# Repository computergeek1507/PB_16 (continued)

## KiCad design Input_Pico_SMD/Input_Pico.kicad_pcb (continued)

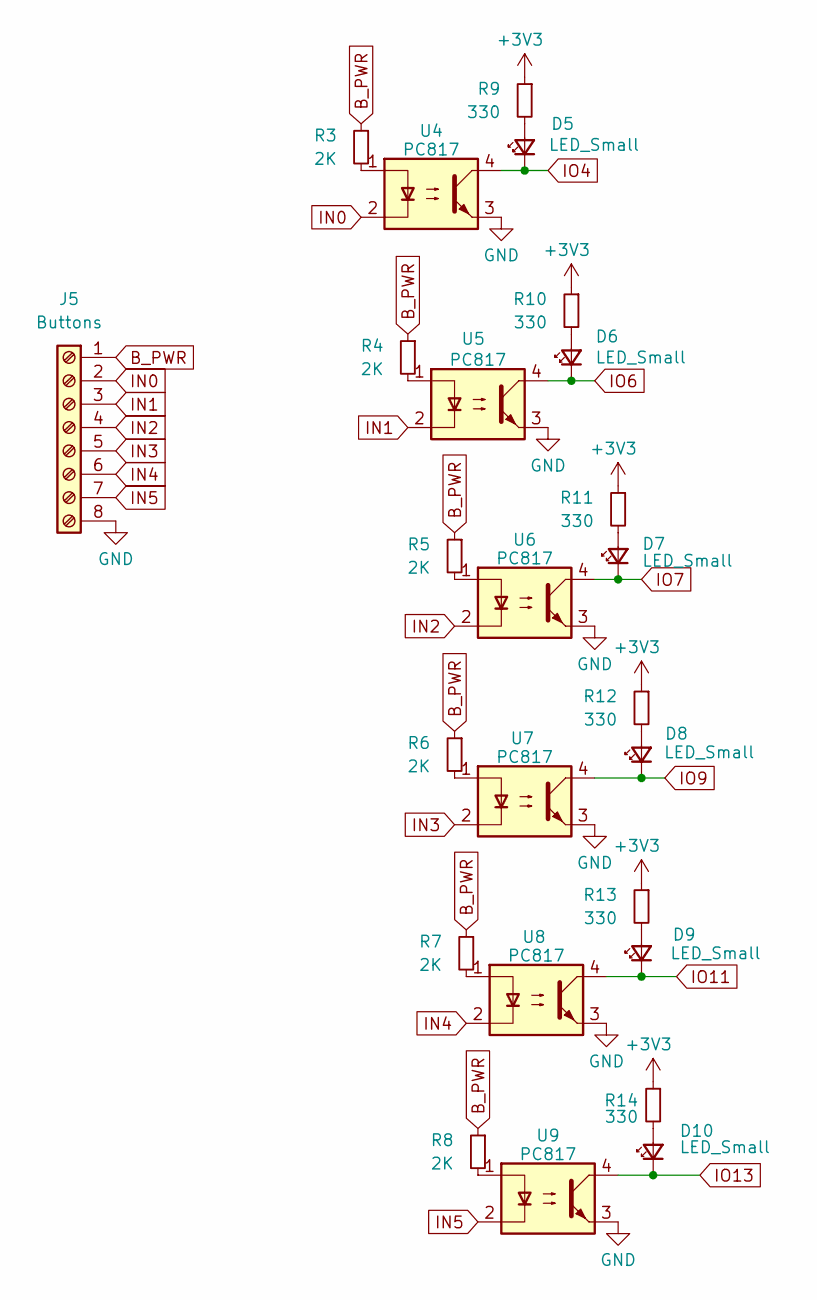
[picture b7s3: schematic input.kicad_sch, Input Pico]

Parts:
D5, D6, D7, D8, D9, D10: LED_Small; LED_0603_1608Metric; LCSC_PN C2286
J5: Buttons; PhoenixContact_MCV_1,5_8-G-5.08_1x08_P5.08mm_Vertical
R3, R4, R5, R6, R7, R8: 2K; R_0603_1608Metric; LCSC_PN C21190
R9, R10, R11, R12, R13, R14: 330; R_0603_1608Metric; LCSC_PN C22962
U4, U5, U6, U7, U8, U9: PC817; DIP-4_W7.62mm; LCSC_PN C5350

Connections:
+3V3: R9.1, R10.1, R11.1, R12.1, R13.1, R14.1; also elsewhere on the board
B_PWR: J5.1, R3.1, R4.1, R5.1, R6.1, R7.1, R8.1; also elsewhere on the board
GND: J5.8, U4.3, U5.3, U6.3, U7.3, U8.3, U9.3; also elsewhere on the board
IN0: J5.2, U4.2
IN1: J5.3, U5.2
IN2: J5.4, U6.2
IN3: J5.5, U7.2
IN4: J5.6, U8.2
IN5: J5.7, U9.2
IO4: D5.1 (K), U4.4; also elsewhere on the board
IO6: D6.1 (K), U5.4; also elsewhere on the board
IO7: D7.1 (K), U6.4; also elsewhere on the board
IO9: D8.1 (K), U7.4; also elsewhere on the board
IO11: D9.1 (K), U8.4; also elsewhere on the board
IO13: D10.1 (K), U9.4; also elsewhere on the board
unnamed: D5.2 (A), R9.2
unnamed: D6.2 (A), R10.2
unnamed: D7.2 (A), R11.2
unnamed: D8.2 (A), R12.2
unnamed: D9.2 (A), R13.2
unnamed: D10.2 (A), R14.2
unnamed: R3.2, U4.1
unnamed: R4.2, U5.1
unnamed: R5.2, U6.1
unnamed: R6.2, U7.1
unnamed: R7.2, U8.1
unnamed: R8.2, U9.1

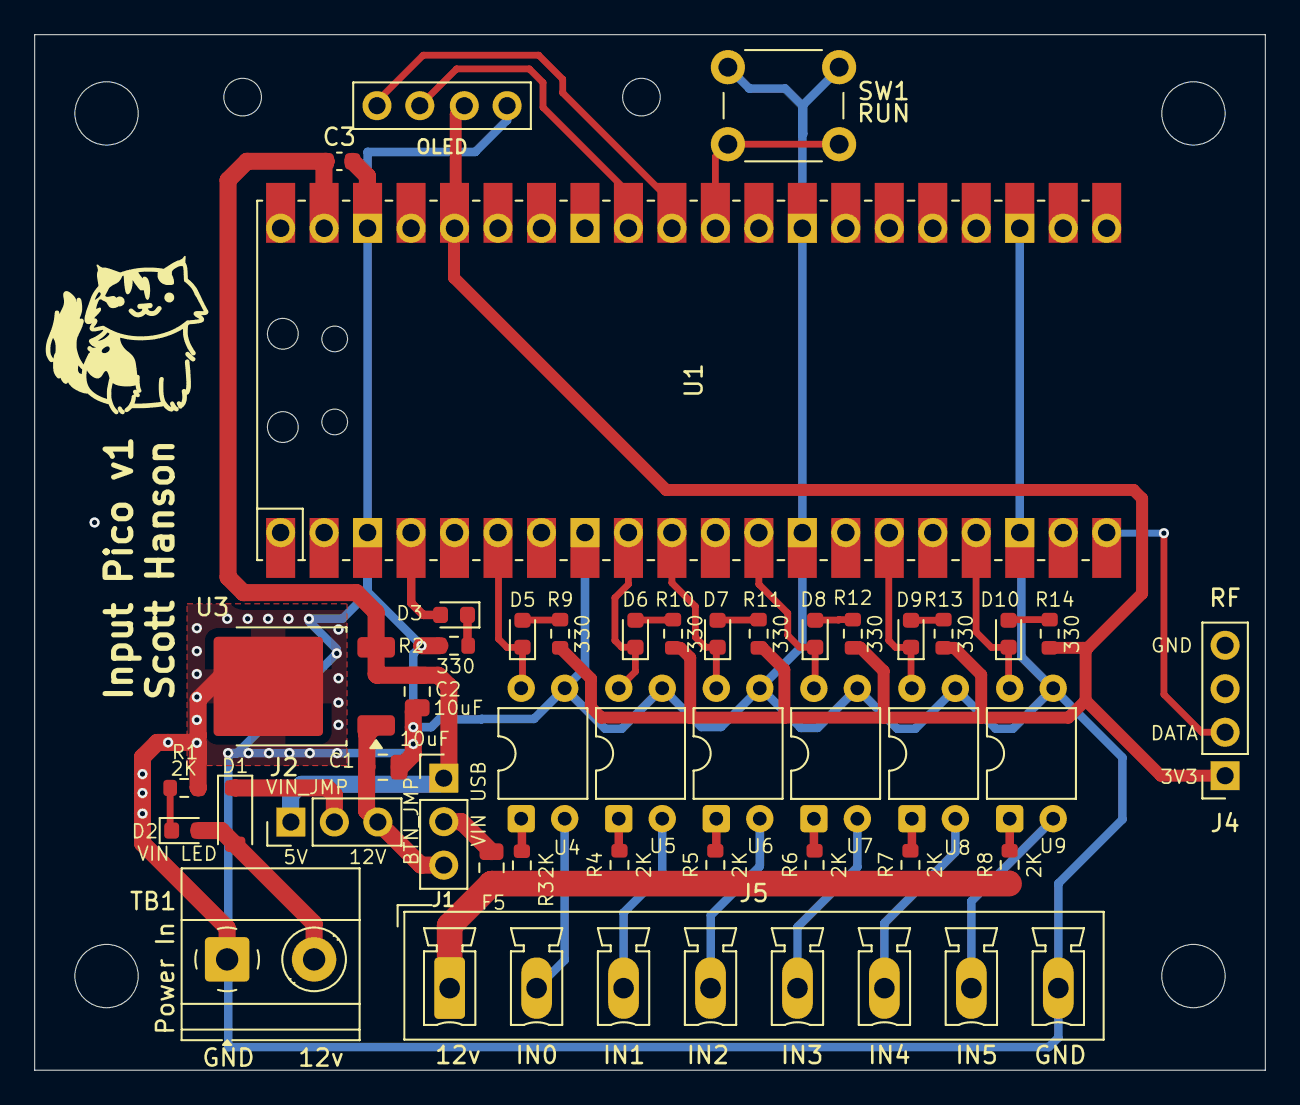
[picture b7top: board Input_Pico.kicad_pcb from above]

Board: 2 copper layers, 71.9 x 60.5 mm, 46 parts (0 on the bottom side), 39 nets.

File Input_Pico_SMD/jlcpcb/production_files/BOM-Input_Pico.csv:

Comment,Designator,Footprint,LCSC,Quantity
0.1uF,C3,C_0603_1608Metric,C14663,1
10uF,"C1,C2",C_0805_2012Metric,C15850,2
OLED,J3,OLED-SSD1306-128X64-I2C-THT,C225501,1
LED_Small,"D10,D2,D3,D5,D6,D7,D8,D9",LED_0603_1608Metric,C2286,8
330,"R10,R11,R12,R13,R14,R2,R9",R_0603_1608Metric,C23138,7
Button_Fuse,F5,Fuse_0805_2012Metric,C261938,1
Power In,TB1,"TerminalBlock_Phoenix_MKDS-1,5-2-5.08_1x02_P5.08mm_Horizontal",C306200,1
2K,"R1,R3,R4,R5,R6,R7,R8",R_0603_1608Metric,C4190,7
BTN_JMP,"J1,J2",PinHeader_1x03_P2.54mm_Vertical,C49257,2
PC817,"U4,U5,U6,U7,U8,U9",DIP-4_W7.62mm,C5350,6
L7805,U3,TO-252-2,C58069,1
Buttons,"J5,SW1","PhoenixContact_MCV_1,5_8-G-5.08_1x08_P5.08mm_Vertical",C83205,2
B5819W,D1,D_SOD-123,C8598,1
Pico,U1,RPi_Pico_W5500_SMD_TH,,1
RF,J4,PinSocket_1x04_P2.54mm_Vertical,,1

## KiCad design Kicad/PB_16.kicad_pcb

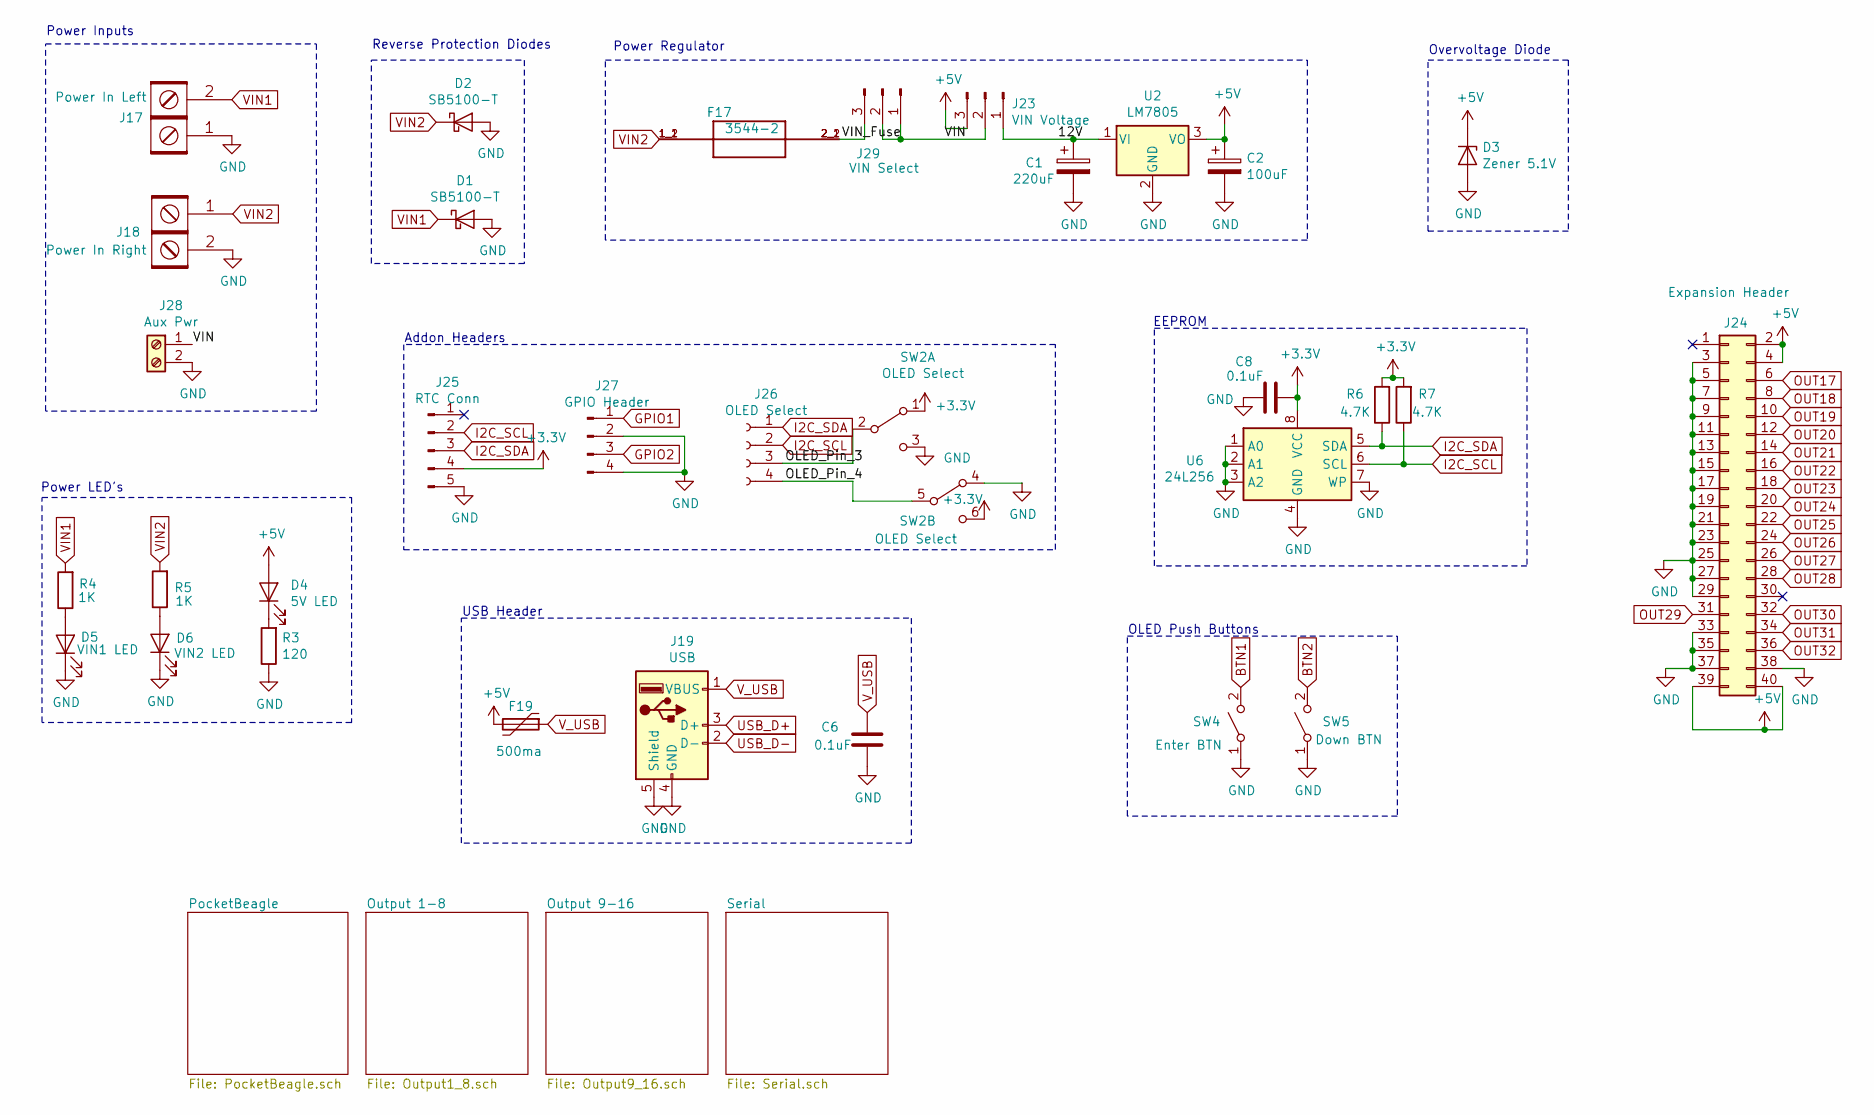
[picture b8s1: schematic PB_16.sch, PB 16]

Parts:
C1: 220uF; CP_Radial_D10.0mm_P5.00mm; MPN ECA-1HM221; Digi-Key_PN P5183-ND
C2: 100uF; CP_Radial_D5.0mm_P2.00mm; MPN 16ZLH100MEFC5X11; Digi-Key_PN 1189-1148-ND
C6, C8: 0.1uF; C_Rect_L7.0mm_W2.0mm_P5.00mm; MPN SR215C104KARTR1; Digi-Key_PN 478-7336-1-ND
D1, D2: SB5100-T; D_DO-201AD_P12.70mm_Horizontal; MPN SB5100-T; Digi-Key_PN SB5100DICT-ND
D3: Zener 5.1V; D_5W_P10.16mm_Horizontal; MPN 1N5338BRLG; Digi-Key_PN 1N5338BRLGOSCT-ND
D4: 5V LED; LED_D3.0mm_Clear; MPN WP3A8GD; Digi-Key_PN 754-1217-ND
D5: VIN1 LED; LED_D3.0mm_Clear; MPN WP3A8GD; Digi-Key_PN 754-1217-ND
D6: VIN2 LED; LED_D3.0mm_Clear; MPN WP3A8GD; Digi-Key_PN 754-1217-ND
F17: 3544-2; FUSE_3544-2; MPN 3544-2; Digi-Key_PN 36-3544-2-ND
F19: 500ma; Fuse_BelFuse_0ZRE0005FF_L8.3mm_W3.8mm; MPN RXEF050-2; Digi-Key_PN RXEF050-2HFCT-ND
J17: Power In Left; BARRIER_BLOCK_1ROW_2POS_P9.5MM; MPN OSTYK51102030; Digi-Key_PN ED2953-ND
J18: Power In Right; BARRIER_BLOCK_1ROW_2POS_P9.5MM; MPN OSTYK51102030; Digi-Key_PN ED2953-ND
J19: USB; USB_A_Molex_105057_Vertical; MPN 1050570001; Digi-Key_PN WM8672-ND
J23: VIN Voltage; PinHeader_1x03_P2.54mm_Vertical; MPN 61300311121; Digi-Key_PN 732-5316-ND
J24: Expansion Header; IDC-Header_2x20_P2.54mm_Vertical; MPN SBH11-PBPC-D20-ST-BK; Digi-Key_PN S9175-ND
J25: RTC Conn; PinHeader_1x05_P2.54mm_Vertical; MPN 61300511121; Digi-Key_PN 732-5318-ND
J26: OLED Select; PinSocket_1x04_P2.54mm_Vertical; MPN PPTC041LFBN-RC; Digi-Key_PN S7002-ND
J27: GPIO Header; JST_XH_B4B-XH-A_1x04_P2.50mm_Vertical; MPN B4B-XH-A(LF)(SN); Digi-Key_PN 455-2249-ND
J28: Aux Pwr; PHOENIX_MKDS1%2f2-3.81; MPN 1727010; Digi-Key_PN 277-1947-ND
J29: VIN Select; PinHeader_1x03_P2.54mm_Vertical; MPN 61300311121; Digi-Key_PN 732-5316-ND
R3: 120; R_Axial_DIN0207_L6.3mm_D2.5mm_P7.62mm_Horizontal; MPN CF14JT120R; Digi-Key_PN CF14JT120RCT-ND
R4, R5: 1K; R_Axial_DIN0207_L6.3mm_D2.5mm_P7.62mm_Horizontal; MPN CF14JT1K00; Digi-Key_PN CF14JT1K00CT-ND
R6, R7: 4.7K; R_Axial_DIN0207_L6.3mm_D2.5mm_P7.62mm_Horizontal; MPN CF14JT4K70; Digi-Key_PN CF14JT4K70CT-ND
SW2: OLED Select; SW_CuK_JS202011CQN_DPDT_Straight; MPN JS202011CQN; Digi-Key_PN 401-2001-ND
SW4: Enter BTN; SW_PUSH_6mm; MPN 1825910-6; Digi-Key_PN 450-1650-ND
SW5: Down BTN; SW_PUSH_6mm; MPN 1825910-6; Digi-Key_PN 450-1650-ND
U2: LM7805; TO-220-3_Vertical; MPN OKI-78SR-5/1.5-W36-C; Digi-Key_PN 811-2196-5-ND
U6: 24L256; DIP-8_W7.62mm; MPN FT24C256A-UDR-B; Digi-Key_PN 1219-1052-ND

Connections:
+3V3: C8.1, J25.4, R6.2, R7.2, SW2.1 (A), SW2.6 (C), U6.8 (VCC); also elsewhere on the board
+5V: C2.1, D3.1 (K), D4.2 (A), F19.2, J23.3, J24.2, J24.4, J24.39, J24.40, U2.3 (VO); also elsewhere on the board
/12V: C1.1, J23.1, U2.1 (VI)
/OLED_Pin_3: J26.3, SW2.2 (B)
/OLED_Pin_4: J26.4, SW2.5 (B)
/VIN: J23.2, J28.1, J29.1, J29.2
/VIN_Fuse: F17.2_1 (2), F17.2_2 (2), J29.3
BTN1: SW4.2 (B); also elsewhere on the board
BTN2: SW5.2 (B); also elsewhere on the board
GND: C1.2, C2.2, C6.2, C8.2, D1.2 (A), D2.2 (A), D3.2 (A), D5.1 (K), D6.1 (K), J17.1, J18.2, J19.4 (GND), J19.5 (Shield), J24.3, J24.5, J24.7, J24.9, J24.11, J24.13, J24.15, J24.17, J24.19, J24.21, J24.23, J24.25, J24.27, J24.29, J24.33, J24.35, J24.37, J24.38, J25.5, J27.2, J27.4, J28.2, R3.1, SW2.3 (C), SW2.4 (A), SW4.1 (A), SW5.1 (A), U2.2 (GND), U6.1 (A0), U6.2 (A1), U6.3 (A2), U6.4 (GND), U6.7 (WP); also elsewhere on the board
GPIO1: J27.1; also elsewhere on the board
GPIO2: J27.3; also elsewhere on the board
I2C_SCL: J25.2, J26.2, R7.1, U6.6 (SCL); also elsewhere on the board
I2C_SDA: J25.3, J26.1, R6.1, U6.5 (SDA); also elsewhere on the board
unnamed: D4.1 (K), R3.2
unnamed: D5.2 (A), R4.1
unnamed: D6.2 (A), R5.1
OUT17: J24.6; also elsewhere on the board
OUT18: J24.8; also elsewhere on the board
OUT19: J24.10; also elsewhere on the board
OUT20: J24.12; also elsewhere on the board
OUT21: J24.14; also elsewhere on the board
OUT22: J24.16; also elsewhere on the board
OUT23: J24.18; also elsewhere on the board
OUT24: J24.20; also elsewhere on the board
OUT25: J24.22; also elsewhere on the board
OUT26: J24.24; also elsewhere on the board
OUT27: J24.26; also elsewhere on the board
OUT28: J24.28; also elsewhere on the board
OUT29: J24.31; also elsewhere on the board
OUT30: J24.32; also elsewhere on the board
OUT31: J24.34; also elsewhere on the board
OUT32: J24.36; also elsewhere on the board
USB_D+: J19.3 (D+); also elsewhere on the board
USB_D-: J19.2 (D-); also elsewhere on the board
VIN1: D1.1 (K), J17.2, R4.2; also elsewhere on the board
VIN2: D2.1 (K), F17.1_1 (1), F17.1_2 (1), J18.1, R5.2; also elsewhere on the board
V_USB: C6.1, F19.1, J19.1 (VBUS); also elsewhere on the board

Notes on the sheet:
Power Inputs
Reverse Protection Diodes
Power Regulator
Overvoltage Diode
Power LED's
Addon Headers
EEPROM
USB Header
OLED Push Buttons

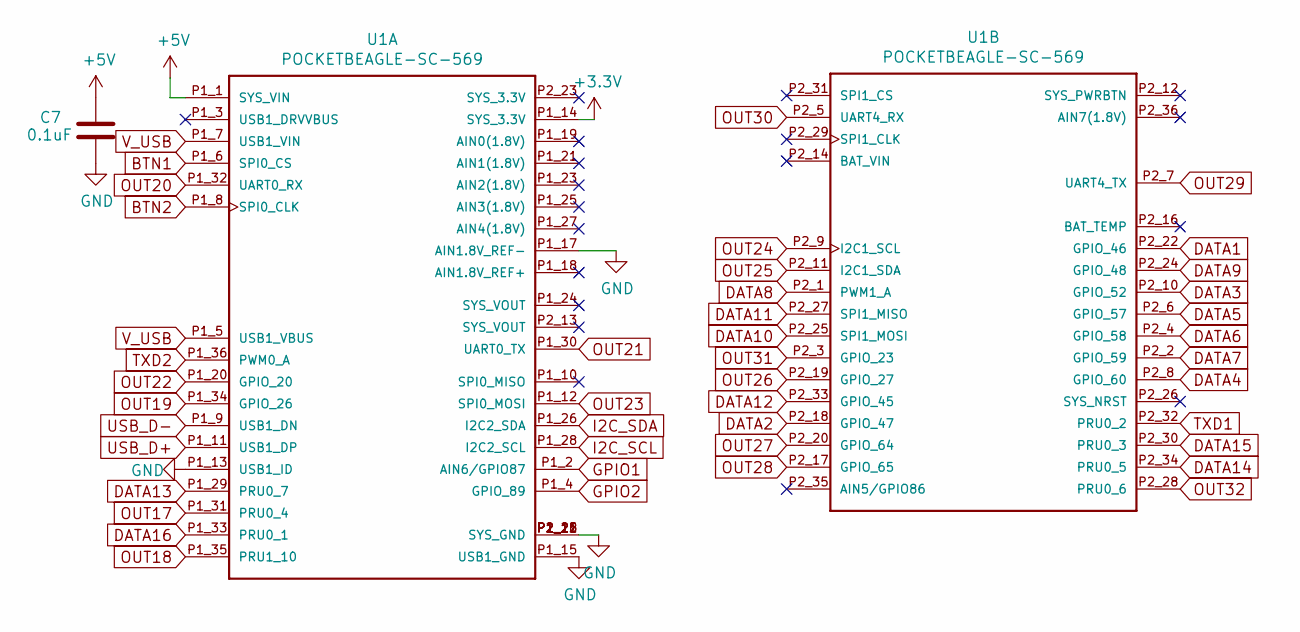
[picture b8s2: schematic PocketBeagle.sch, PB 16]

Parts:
C7: 0.1uF; C_Rect_L7.0mm_W2.0mm_P5.00mm; MPN SR215C104KARTR1; Digi-Key_PN 478-7336-1-ND
U1: POCKETBEAGLE-SC-569; BEAGLE_POCKETBEAGLE-SC-569; MPN POCKETBEAGLE-SC-569; Digi-Key_PN POCKETBEAGLE-SC-569-ND

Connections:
+3V3: U1.P1_14 (SYS_3.3V); also elsewhere on the board
+5V: C7.1, U1.P1_1 (SYS_VIN); also elsewhere on the board
BTN1: U1.P1_6 (SPI0_CS); also elsewhere on the board
BTN2: U1.P1_8 (SPI0_CLK); also elsewhere on the board
DATA1: U1.P2_22 (GPIO_46); also elsewhere on the board
DATA2: U1.P2_18 (GPIO_47); also elsewhere on the board
DATA3: U1.P2_10 (GPIO_52); also elsewhere on the board
DATA4: U1.P2_8 (GPIO_60); also elsewhere on the board
DATA5: U1.P2_6 (GPIO_57); also elsewhere on the board
DATA6: U1.P2_4 (GPIO_58); also elsewhere on the board
DATA7: U1.P2_2 (GPIO_59); also elsewhere on the board
DATA8: U1.P2_1 (PWM1_A); also elsewhere on the board
DATA9: U1.P2_24 (GPIO_48); also elsewhere on the board
DATA10: U1.P2_25 (SPI1_MOSI); also elsewhere on the board
DATA11: U1.P2_27 (SPI1_MISO); also elsewhere on the board
DATA12: U1.P2_33 (GPIO_45); also elsewhere on the board
DATA13: U1.P1_29 (PRU0_7); also elsewhere on the board
DATA14: U1.P2_34 (PRU0_5); also elsewhere on the board
DATA15: U1.P2_30 (PRU0_3); also elsewhere on the board
DATA16: U1.P1_33 (PRU0_1); also elsewhere on the board
GND: C7.2, U1.P1_13 (USB1_ID), U1.P1_15 (USB1_GND), U1.P1_16 (SYS_GND), U1.P1_17 (AIN1.8V_REF-), U1.P1_22 (SYS_GND), U1.P2_15 (SYS_GND), U1.P2_21 (SYS_GND); also elsewhere on the board
GPIO1: U1.P1_2 (AIN6/GPIO87); also elsewhere on the board
GPIO2: U1.P1_4 (GPIO_89); also elsewhere on the board
I2C_SCL: U1.P1_28 (I2C2_SCL); also elsewhere on the board
I2C_SDA: U1.P1_26 (I2C2_SDA); also elsewhere on the board
OUT17: U1.P1_31 (PRU0_4); also elsewhere on the board
OUT18: U1.P1_35 (PRU1_10); also elsewhere on the board
OUT19: U1.P1_34 (GPIO_26); also elsewhere on the board
OUT20: U1.P1_32 (UART0_RX); also elsewhere on the board
OUT21: U1.P1_30 (UART0_TX); also elsewhere on the board
OUT22: U1.P1_20 (GPIO_20); also elsewhere on the board
OUT23: U1.P1_12 (SPI0_MOSI); also elsewhere on the board
OUT24: U1.P2_9 (I2C1_SCL); also elsewhere on the board
OUT25: U1.P2_11 (I2C1_SDA); also elsewhere on the board
OUT26: U1.P2_19 (GPIO_27); also elsewhere on the board
OUT27: U1.P2_20 (GPIO_64); also elsewhere on the board
OUT28: U1.P2_17 (GPIO_65); also elsewhere on the board
OUT29: U1.P2_7 (UART4_TX); also elsewhere on the board
OUT30: U1.P2_5 (UART4_RX); also elsewhere on the board
OUT31: U1.P2_3 (GPIO_23); also elsewhere on the board
OUT32: U1.P2_28 (PRU0_6); also elsewhere on the board
TXD1: U1.P2_32 (PRU0_2); also elsewhere on the board
TXD2: U1.P1_36 (PWM0_A); also elsewhere on the board
USB_D+: U1.P1_11 (USB1_DP); also elsewhere on the board
USB_D-: U1.P1_9 (USB1_DN); also elsewhere on the board
V_USB: U1.P1_5 (USB1_VBUS), U1.P1_7 (USB1_VIN); also elsewhere on the board

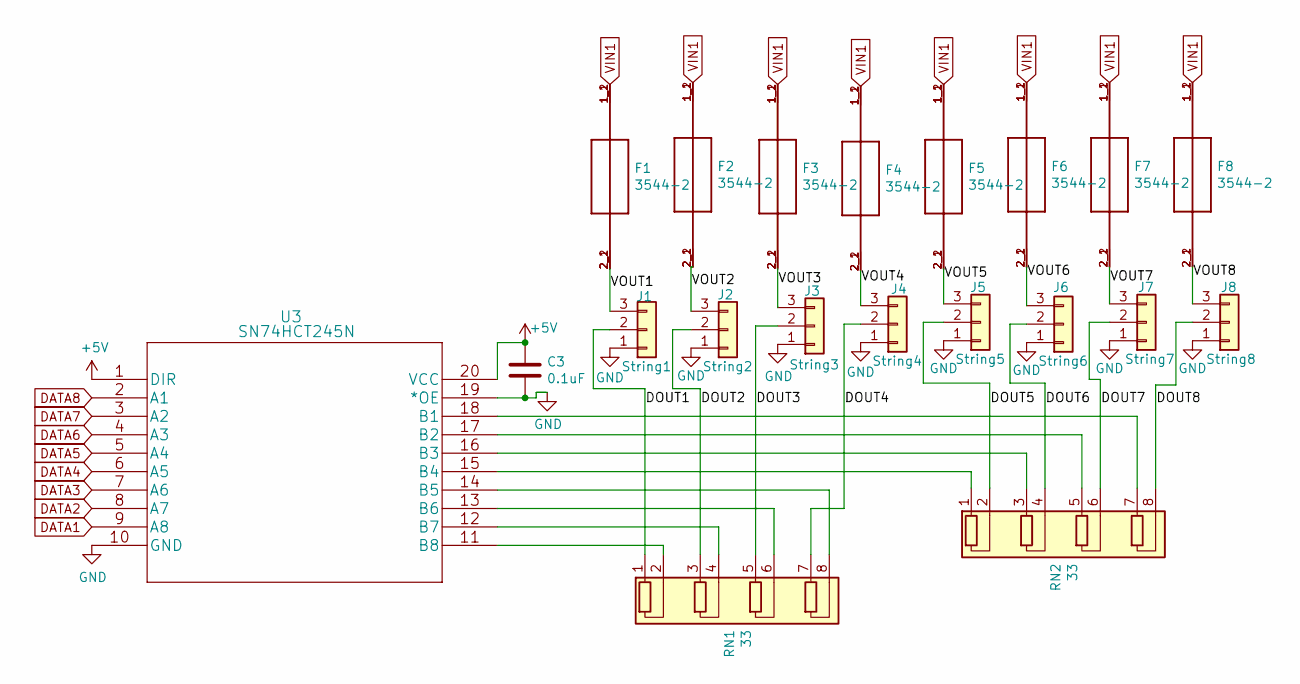
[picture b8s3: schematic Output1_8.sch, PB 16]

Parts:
C3: 0.1uF; C_Rect_L7.0mm_W2.0mm_P5.00mm; MPN SR215C104KARTR1; Digi-Key_PN 478-7336-1-ND
F1, F2, F3, F4, F5, F6, F7, F8: 3544-2; FUSE_3544-2; MPN 3544-2; Digi-Key_PN 36-3544-2-ND
J1: String1; PhoenixContact_MCV_1,5_3-G-3.5_1x03_P3.50mm_Vertical; MPN 1843619/OSTTJ0311530; Digi-Key_PN 277-5737-ND/ED10555-ND
J2: String2; PhoenixContact_MCV_1,5_3-G-3.5_1x03_P3.50mm_Vertical; MPN 1843619/OSTTJ0311530; Digi-Key_PN 277-5737-ND/ED10555-ND
J3: String3; PhoenixContact_MCV_1,5_3-G-3.5_1x03_P3.50mm_Vertical; MPN 1843619/OSTTJ0311530; Digi-Key_PN 277-5737-ND/ED10555-ND
J4: String4; PhoenixContact_MCV_1,5_3-G-3.5_1x03_P3.50mm_Vertical; MPN 1843619/OSTTJ0311530; Digi-Key_PN 277-5737-ND/ED10555-ND
J5: String5; PhoenixContact_MCV_1,5_3-G-3.5_1x03_P3.50mm_Vertical; MPN 1843619/OSTTJ0311530; Digi-Key_PN 277-5737-ND/ED10555-ND
J6: String6; PhoenixContact_MCV_1,5_3-G-3.5_1x03_P3.50mm_Vertical; MPN 1843619/OSTTJ0311530; Digi-Key_PN 277-5737-ND/ED10555-ND
J7: String7; PhoenixContact_MCV_1,5_3-G-3.5_1x03_P3.50mm_Vertical; MPN 1843619/OSTTJ0311530; Digi-Key_PN 277-5737-ND/ED10555-ND
J8: String8; PhoenixContact_MCV_1,5_3-G-3.5_1x03_P3.50mm_Vertical; MPN 1843619/OSTTJ0311530; Digi-Key_PN 277-5737-ND/ED10555-ND
RN1, RN2: 33; R_Array_SIP8; MPN 4608X-102-330LF; Digi-Key_PN 4608X-2-330LF-ND
U3: SN74HCT245N; MPN SN74HCT245N; Digi-Key_PN 296-1612-5-ND

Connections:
+5V: C3.1, U3.1 (DIR), U3.20 (VCC); also elsewhere on the board
/Output 1-8/DOUT1: J1.2, RN1.1 (R1.1)
/Output 1-8/DOUT2: J2.2, RN1.3 (R2.1)
/Output 1-8/DOUT3: J3.2, RN1.5 (R3.1)
/Output 1-8/DOUT4: J4.2, RN1.7 (R4.1)
/Output 1-8/DOUT5: J5.2, RN2.2 (R1.2)
/Output 1-8/DOUT6: J6.2, RN2.4 (R2.2)
/Output 1-8/DOUT7: J7.2, RN2.6 (R3.2)
/Output 1-8/DOUT8: J8.2, RN2.8 (R4.2)
/Output 1-8/VOUT1: F1.2_1 (2), F1.2_2 (2), J1.3
/Output 1-8/VOUT2: F2.2_1 (2), F2.2_2 (2), J2.3
/Output 1-8/VOUT3: F3.2_1 (2), F3.2_2 (2), J3.3
/Output 1-8/VOUT4: F4.2_1 (2), F4.2_2 (2), J4.3
/Output 1-8/VOUT5: F5.2_1 (2), F5.2_2 (2), J5.3
/Output 1-8/VOUT6: F6.2_1 (2), F6.2_2 (2), J6.3
/Output 1-8/VOUT7: F7.2_1 (2), F7.2_2 (2), J7.3
/Output 1-8/VOUT8: F8.2_1 (2), F8.2_2 (2), J8.3
DATA1: U3.9 (A8); also elsewhere on the board
DATA2: U3.8 (A7); also elsewhere on the board
DATA3: U3.7 (A6); also elsewhere on the board
DATA4: U3.6 (A5); also elsewhere on the board
DATA5: U3.5 (A4); also elsewhere on the board
DATA6: U3.4 (A3); also elsewhere on the board
DATA7: U3.3 (A2); also elsewhere on the board
DATA8: U3.2 (A1); also elsewhere on the board
GND: C3.2, J1.1, J2.1, J3.1, J4.1, J5.1, J6.1, J7.1, J8.1, U3.10 (GND), U3.19 (*OE); also elsewhere on the board
unnamed: RN1.2 (R1.2), U3.11 (B8)
unnamed: RN1.4 (R2.2), U3.12 (B7)
unnamed: RN1.6 (R3.2), U3.13 (B6)
unnamed: RN1.8 (R4.2), U3.14 (B5)
unnamed: RN2.1 (R1.1), U3.15 (B4)
unnamed: RN2.3 (R2.1), U3.16 (B3)
unnamed: RN2.5 (R3.1), U3.17 (B2)
unnamed: RN2.7 (R4.1), U3.18 (B1)
VIN1: F1.1_1 (1), F1.1_2 (1), F2.1_1 (1), F2.1_2 (1), F3.1_1 (1), F3.1_2 (1), F4.1_1 (1), F4.1_2 (1), F5.1_1 (1), F5.1_2 (1), F6.1_1 (1), F6.1_2 (1), F7.1_1 (1), F7.1_2 (1), F8.1_1 (1), F8.1_2 (1); also elsewhere on the board

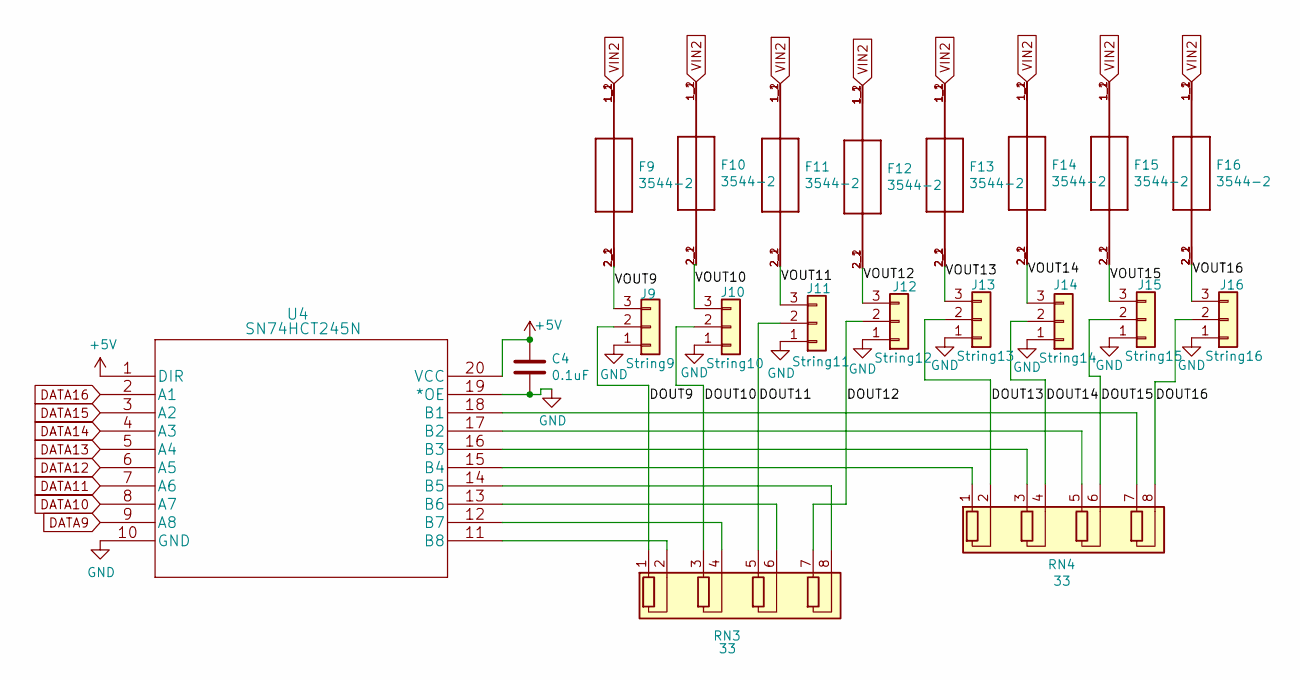
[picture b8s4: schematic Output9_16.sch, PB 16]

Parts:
C4: 0.1uF; C_Rect_L7.0mm_W2.0mm_P5.00mm; MPN SR215C104KARTR1; Digi-Key_PN 478-7336-1-ND
F9, F10, F11, F12, F13, F14, F15, F16: 3544-2; FUSE_3544-2; MPN 3544-2; Digi-Key_PN 36-3544-2-ND
J9: String9; PhoenixContact_MCV_1,5_3-G-3.5_1x03_P3.50mm_Vertical; MPN 1843619/OSTTJ0311530; Digi-Key_PN 277-5737-ND/ED10555-ND
J10: String10; PhoenixContact_MCV_1,5_3-G-3.5_1x03_P3.50mm_Vertical; MPN 1843619/OSTTJ0311530; Digi-Key_PN 277-5737-ND/ED10555-ND
J11: String11; PhoenixContact_MCV_1,5_3-G-3.5_1x03_P3.50mm_Vertical; MPN 1843619/OSTTJ0311530; Digi-Key_PN 277-5737-ND/ED10555-ND
J12: String12; PhoenixContact_MCV_1,5_3-G-3.5_1x03_P3.50mm_Vertical; MPN 1843619/OSTTJ0311530; Digi-Key_PN 277-5737-ND/ED10555-ND
J13: String13; PhoenixContact_MCV_1,5_3-G-3.5_1x03_P3.50mm_Vertical; MPN 1843619/OSTTJ0311530; Digi-Key_PN 277-5737-ND/ED10555-ND
J14: String14; PhoenixContact_MCV_1,5_3-G-3.5_1x03_P3.50mm_Vertical; MPN 1843619/OSTTJ0311530; Digi-Key_PN 277-5737-ND/ED10555-ND
J15: String15; PhoenixContact_MCV_1,5_3-G-3.5_1x03_P3.50mm_Vertical; MPN 1843619/OSTTJ0311530; Digi-Key_PN 277-5737-ND/ED10555-ND
J16: String16; PhoenixContact_MCV_1,5_3-G-3.5_1x03_P3.50mm_Vertical; MPN 1843619/OSTTJ0311530; Digi-Key_PN 277-5737-ND/ED10555-ND
RN3, RN4: 33; R_Array_SIP8; MPN 4608X-102-330LF; Digi-Key_PN 4608X-2-330LF-ND
U4: SN74HCT245N; MPN SN74HCT245N; Digi-Key_PN 296-1612-5-ND

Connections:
+5V: C4.1, U4.1 (DIR), U4.20 (VCC); also elsewhere on the board
/Output 9-16/DOUT9: J9.2, RN3.1 (R1.1)
/Output 9-16/DOUT10: J10.2, RN3.3 (R2.1)
/Output 9-16/DOUT11: J11.2, RN3.5 (R3.1)
/Output 9-16/DOUT12: J12.2, RN3.7 (R4.1)
/Output 9-16/DOUT13: J13.2, RN4.2 (R1.2)
/Output 9-16/DOUT14: J14.2, RN4.4 (R2.2)
/Output 9-16/DOUT15: J15.2, RN4.6 (R3.2)
/Output 9-16/DOUT16: J16.2, RN4.8 (R4.2)
/Output 9-16/VOUT9: F9.2_1 (2), F9.2_2 (2), J9.3
/Output 9-16/VOUT10: F10.2_1 (2), F10.2_2 (2), J10.3
/Output 9-16/VOUT11: F11.2_1 (2), F11.2_2 (2), J11.3
/Output 9-16/VOUT12: F12.2_1 (2), F12.2_2 (2), J12.3
/Output 9-16/VOUT13: F13.2_1 (2), F13.2_2 (2), J13.3
/Output 9-16/VOUT14: F14.2_1 (2), F14.2_2 (2), J14.3
/Output 9-16/VOUT15: F15.2_1 (2), F15.2_2 (2), J15.3
/Output 9-16/VOUT16: F16.2_1 (2), F16.2_2 (2), J16.3
DATA9: U4.9 (A8); also elsewhere on the board
DATA10: U4.8 (A7); also elsewhere on the board
DATA11: U4.7 (A6); also elsewhere on the board
DATA12: U4.6 (A5); also elsewhere on the board
DATA13: U4.5 (A4); also elsewhere on the board
DATA14: U4.4 (A3); also elsewhere on the board
DATA15: U4.3 (A2); also elsewhere on the board
DATA16: U4.2 (A1); also elsewhere on the board
GND: C4.2, J9.1, J10.1, J11.1, J12.1, J13.1, J14.1, J15.1, J16.1, U4.10 (GND), U4.19 (*OE); also elsewhere on the board
unnamed: RN3.2 (R1.2), U4.11 (B8)
unnamed: RN3.4 (R2.2), U4.12 (B7)
unnamed: RN3.6 (R3.2), U4.13 (B6)
unnamed: RN3.8 (R4.2), U4.14 (B5)
unnamed: RN4.1 (R1.1), U4.15 (B4)
unnamed: RN4.3 (R2.1), U4.16 (B3)
unnamed: RN4.5 (R3.1), U4.17 (B2)
unnamed: RN4.7 (R4.1), U4.18 (B1)
VIN2: F9.1_1 (1), F9.1_2 (1), F10.1_1 (1), F10.1_2 (1), F11.1_1 (1), F11.1_2 (1), F12.1_1 (1), F12.1_2 (1), F13.1_1 (1), F13.1_2 (1), F14.1_1 (1), F14.1_2 (1), F15.1_1 (1), F15.1_2 (1), F16.1_1 (1), F16.1_2 (1); also elsewhere on the board

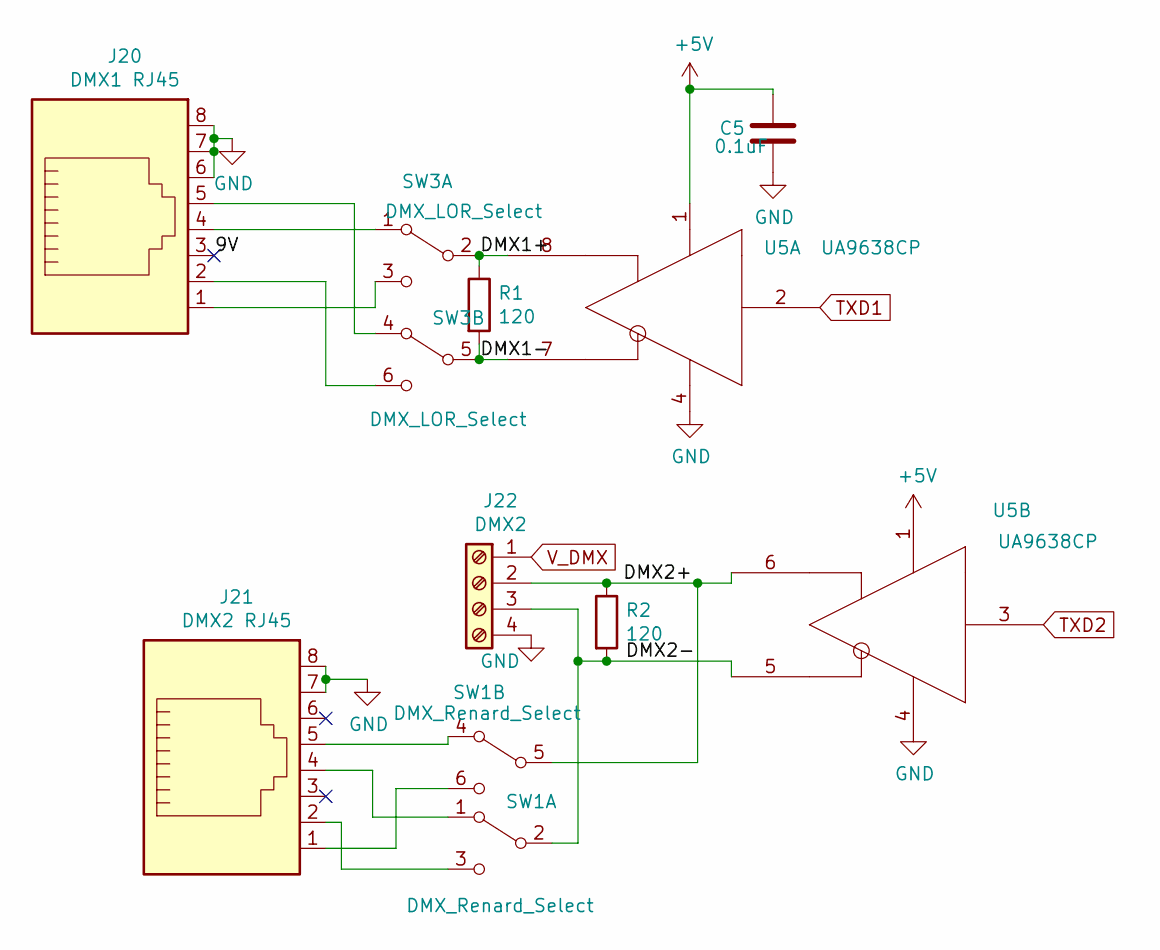
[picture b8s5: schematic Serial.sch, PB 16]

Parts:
C5: 0.1uF; C_Rect_L7.0mm_W2.0mm_P5.00mm; MPN SR215C104KARTR1; Digi-Key_PN 478-7336-1-ND
J20: DMX1 RJ45; RJ45_Amphenol_54602-x08_Horizontal; MPN A-2014-2-4-R; Digi-Key_PN AE10392-ND
J21: DMX2 RJ45; RJ45_Amphenol_54602-x08_Horizontal; MPN A-2014-2-4-R; Digi-Key_PN AE10392-ND
J22: DMX2; TerminalBlock_Phoenix_MKDS-1,5-4_1x04_P5.00mm_Horizontal; MPN 1729034; Digi-Key_PN 277-1238-ND
R1, R2: 120; R_Axial_DIN0207_L6.3mm_D2.5mm_P7.62mm_Horizontal; MPN CF14JT120R; Digi-Key_PN CF14JT120RCT-ND
SW1: DMX_Renard_Select; SW_CuK_JS202011CQN_DPDT_Straight; MPN JS202011CQN; Digi-Key_PN 401-2001-ND
SW3: DMX_LOR_Select; SW_CuK_JS202011CQN_DPDT_Straight; MPN JS202011CQN; Digi-Key_PN 401-2001-ND
U5: UA9638CP; DIP-8_W7.62mm; MPN UA9638CP; Digi-Key_PN 296-15059-5-ND

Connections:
+5V: C5.1, U5.1 (VCC); also elsewhere on the board
/Serial/9V: J20.3
/Serial/DMX1+: R1.1, SW3.2 (B), U5.8 (OUTB)
/Serial/DMX1-: R1.2, SW3.5 (B), U5.7 (OUTA)
/Serial/DMX2+: J22.2, R2.1, SW1.5 (B), U5.6 (OUTB)
/Serial/DMX2-: J22.3, R2.2, SW1.2 (B), U5.5 (OUTA)
GND: C5.2, J20.6, J20.7, J20.8, J21.7, J21.8, J22.4, U5.4 (GND); also elsewhere on the board
unnamed: J20.1, SW3.3 (C)
unnamed: J20.2, SW3.6 (C)
unnamed: J20.4, SW3.1 (A)
unnamed: J20.5, SW3.4 (A)
unnamed: J21.1, SW1.6 (C)
unnamed: J21.2, SW1.3 (C)
unnamed: J21.4, SW1.1 (A)
unnamed: J21.5, SW1.4 (A)
TXD1: U5.2 (IN); also elsewhere on the board
TXD2: U5.3 (IN); also elsewhere on the board
V_DMX: J22.1; also elsewhere on the board

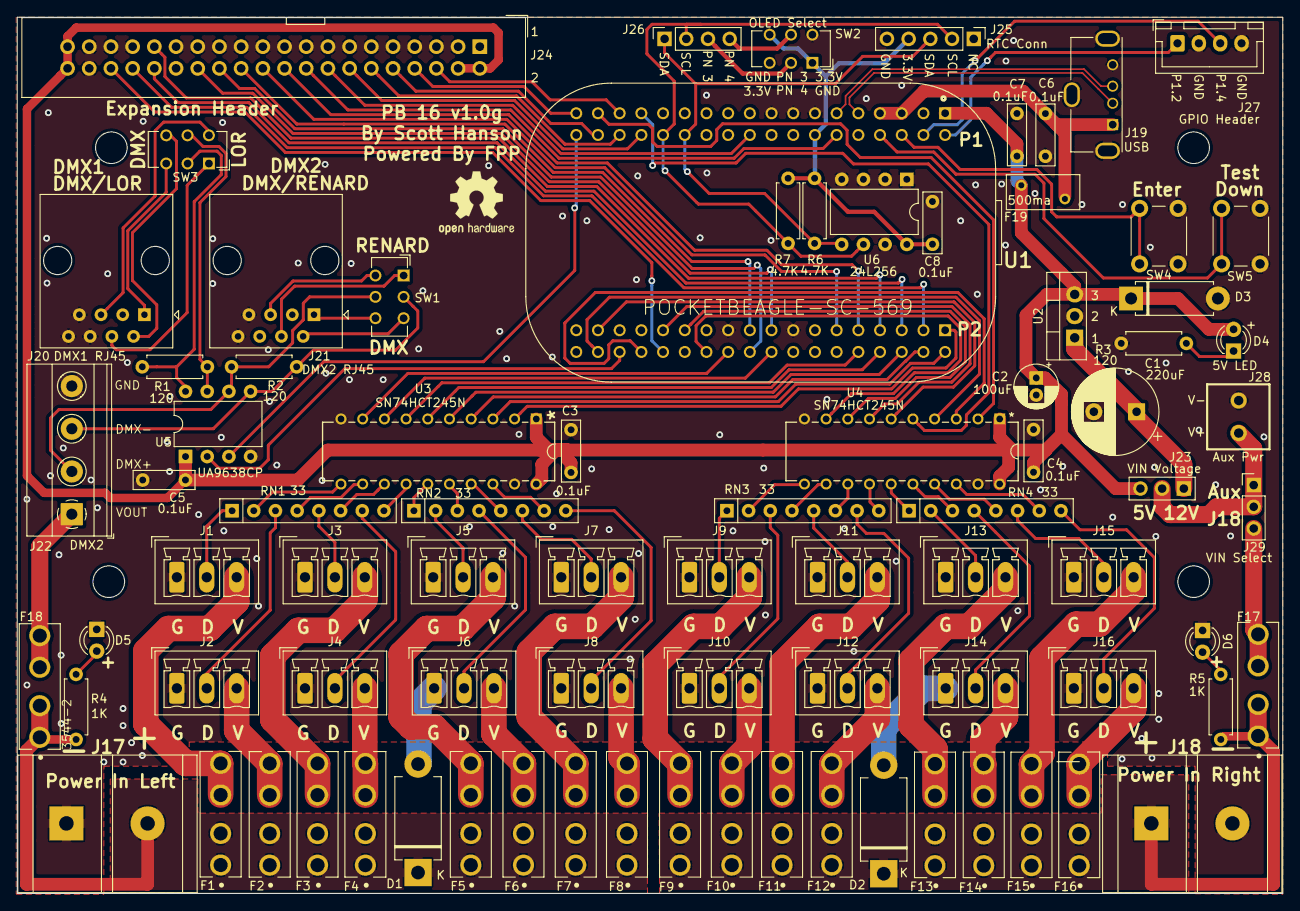
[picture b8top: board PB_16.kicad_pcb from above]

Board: 2 copper layers, 148.1 x 102.6 mm, 84 parts (0 on the bottom side), 117 nets.

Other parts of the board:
F18: 3544-2; FUSE_3544-2

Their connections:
VIN1: F18.1_1, F18.1_2; also elsewhere on the board
V_DMX: F18.2_1, F18.2_2; also elsewhere on the board
